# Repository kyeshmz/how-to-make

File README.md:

https://fab.cba.mit.edu/classes/MAS.863/

```
for img in *.jpg; do [ -f "$img" ] && magick "$img" -resize 1200x "$img"; done
```

https://ui.aceternity.com/components

https://fab.cba.mit.edu/classes/MAS.863/

for hardware
https://fabacademy.org/2022/labs/kamplintfort/students/leen-nijim/assignments/seven.html

#!/bin/bash

# Find all .jpg files in the current directory and subdirectories
find . -type f -name "*.jpg" | while read img; do
    # Resize each image to a width of 1200px, maintaining aspect ratio
    magick "$img" -resize 1200x "$img"
done

ffmpeg -i input_video -vcodec libx264 -b:v 1000k -vf scale=-2:1080 -an output_video.mp4

change mods cut depth to 0.15

for video in ./*.mp4; do ffmpeg -i "$video" -vcodec libx264 -b:v 1000k -vf scale=-2:1080 -an "${video%.*}_reformatted.mp4"; done

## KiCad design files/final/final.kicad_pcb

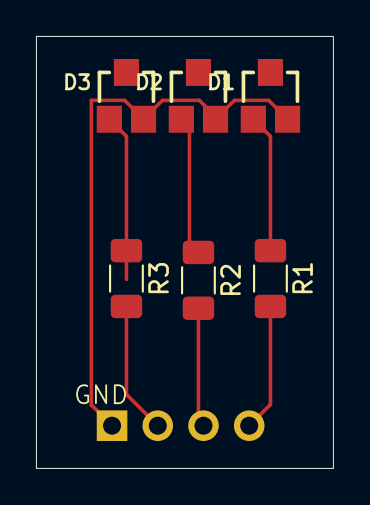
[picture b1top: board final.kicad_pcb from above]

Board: 2 copper layers, 16.5 x 24.0 mm, 7 parts (1 on the bottom side), 7 nets.

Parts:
D1, D2, D3: LED; SML-LX15
J1: Conn_01x04_Pin; PinHeader_1x04_P2.54mm_Horizontal
R1, R2, R3: R; R_1206_3216Metric_Pad1.30x1.75mm_HandSolder

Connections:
unnamed: D1.2 (A), R1.1
unnamed: D1.1 (K), D2.1 (K), D3.1 (K), J1.1
unnamed: D2.2 (A), R2.1
unnamed: D3.2 (A), R3.1
unnamed: J1.2, R3.2
unnamed: J1.3, R2.2
unnamed: J1.4, R1.2

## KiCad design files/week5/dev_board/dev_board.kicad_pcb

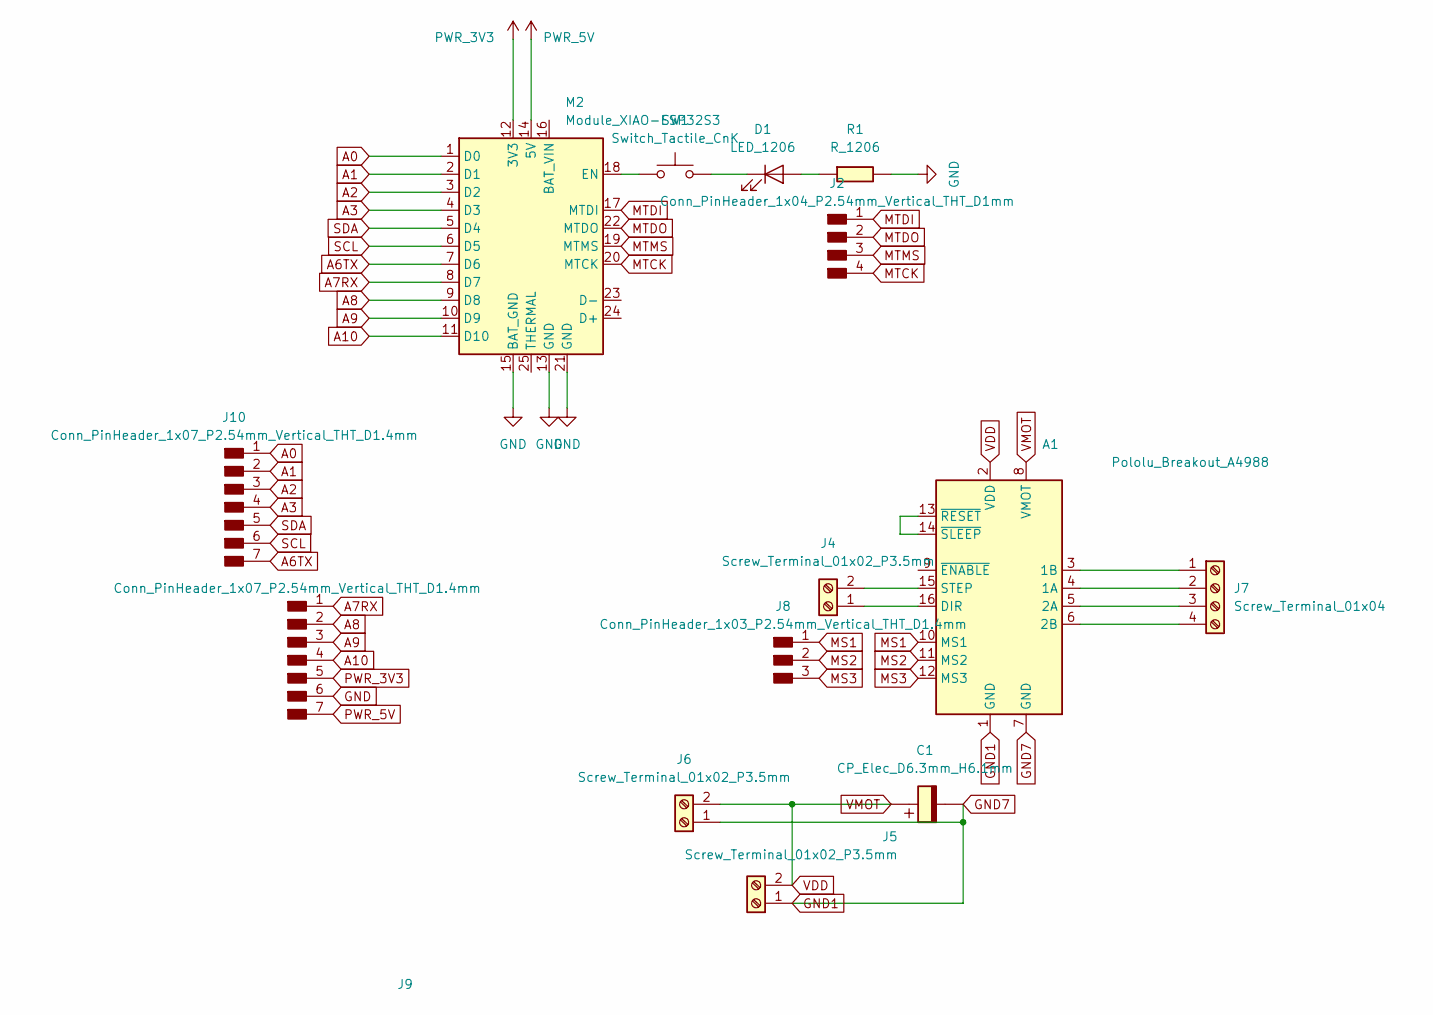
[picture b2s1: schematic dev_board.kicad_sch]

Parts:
A1: Pololu_Breakout_A4988; Pololu_Breakout-16_15.2x20.3mm
C1: CP_Elec_D6.3mm_H6.1mm
D1: LED_1206
J2: Conn_PinHeader_1x04_P2.54mm_Vertical_THT_D1mm; PinHeader_1x04_P2.54mm_Vertical_THT_D1mm
J4, J5, J6: Screw_Terminal_01x02_P3.5mm; TerminalBlock_OnShore_1x02_P3.50mm_Horizontal
J7: Screw_Terminal_01x04
J8: Conn_PinHeader_1x03_P2.54mm_Vertical_THT_D1.4mm; PinHeader_1x03_P2.54mm_Vertical_THT_D1.4mm
J9, J10: Conn_PinHeader_1x07_P2.54mm_Vertical_THT_D1.4mm; PinHeader_1x07_P2.54mm_Vertical_THT_D1.4mm
M2: Module_XIAO-ESP32S3; SeeedStudio_XIAO_ESP32S3
R1: R_1206
SW1: Switch_Tactile_CnK; Button_CnK_PTS636.0_6x3.5mm

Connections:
A0: J10.1, M2.1 (D0)
A1: J10.2, M2.2 (D1)
A2: J10.3, M2.3 (D2)
A3: J10.4, M2.4 (D3)
A6TX: J10.7, M2.7 (D6)
A7RX: J9.1, M2.8 (D7)
A8: J9.2, M2.9 (D8)
A9: J9.3, M2.10 (D9)
A10: J9.4, M2.11 (D10)
GND: J9.6, M2.13 (GND), M2.15 (BAT_GND), M2.21 (GND), R1.1
GND1: A1.1 (GND), A1.7 (GND), C1.2, J5.1, J6.1
MS1: A1.10 (MS1), J8.1
MS2: A1.11 (MS2), J8.2
MS3: A1.12 (MS3), J8.3
MTCK: J2.4, M2.20 (MTCK)
MTDI: J2.1, M2.17 (MTDI)
MTDO: J2.2, M2.22 (MTDO)
MTMS: J2.3, M2.19 (MTMS)
unnamed: A1.4 (1A), J7.2
unnamed: A1.3 (1B), J7.1
unnamed: A1.5 (2A), J7.3
unnamed: A1.6 (2B), J7.4
unnamed: A1.16 (DIR), J4.1
unnamed: A1.15 (STEP), J4.2
unnamed: A1.13 (~RESET), A1.14 (~SLEEP)
unnamed: D1.2 (A), R1.2
unnamed: D1.1 (K), SW1.2
unnamed: M2.18 (EN), SW1.1
PWR_3V3: J9.5, M2.12 (3V3)
PWR_5V: J9.7, M2.14 (5V)
SCL: J10.6, M2.6 (D5)
SDA: J10.5, M2.5 (D4)
VDD: A1.2 (VDD), A1.8 (VMOT), C1.1, J5.2, J6.2

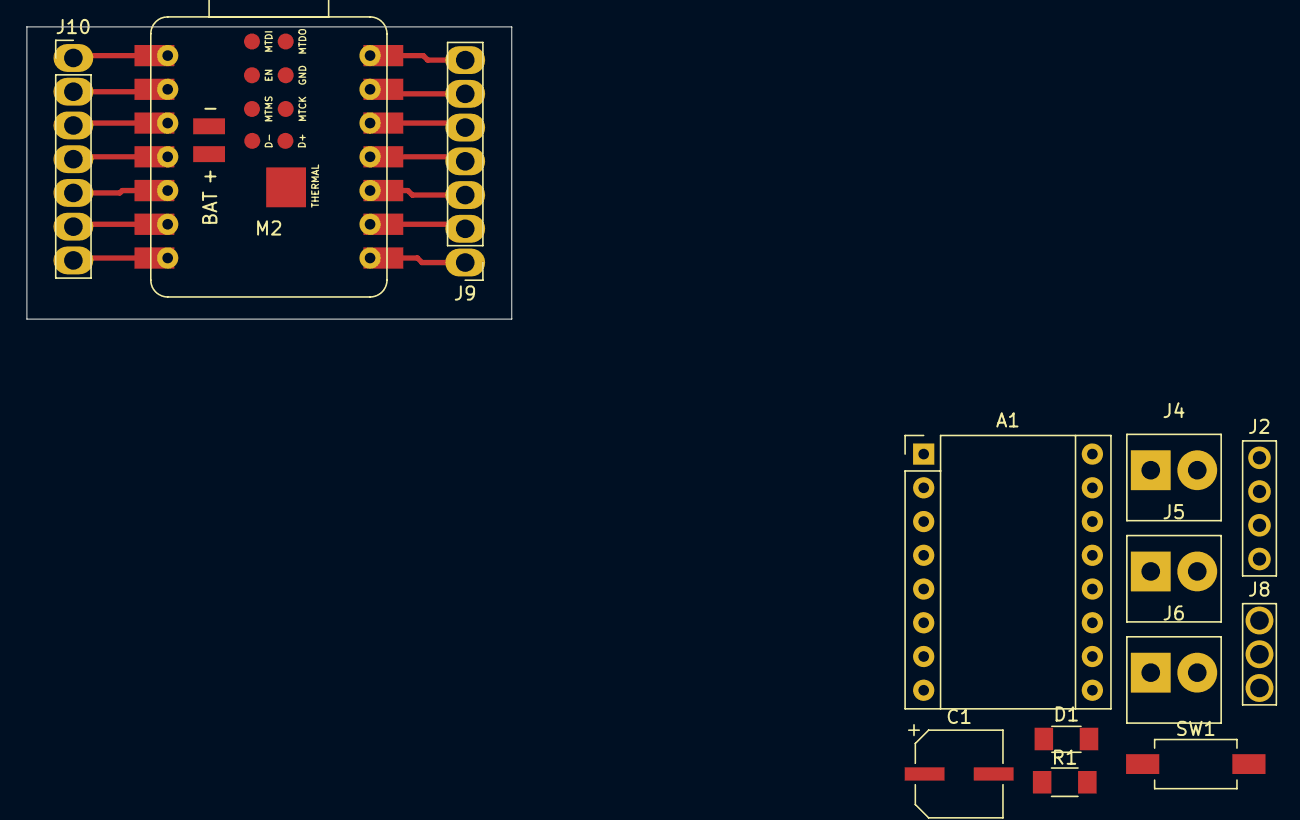
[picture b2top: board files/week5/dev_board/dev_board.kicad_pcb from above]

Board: 2 copper layers, 36.5 x 22.0 mm, 13 parts (0 on the bottom side), 29 nets.

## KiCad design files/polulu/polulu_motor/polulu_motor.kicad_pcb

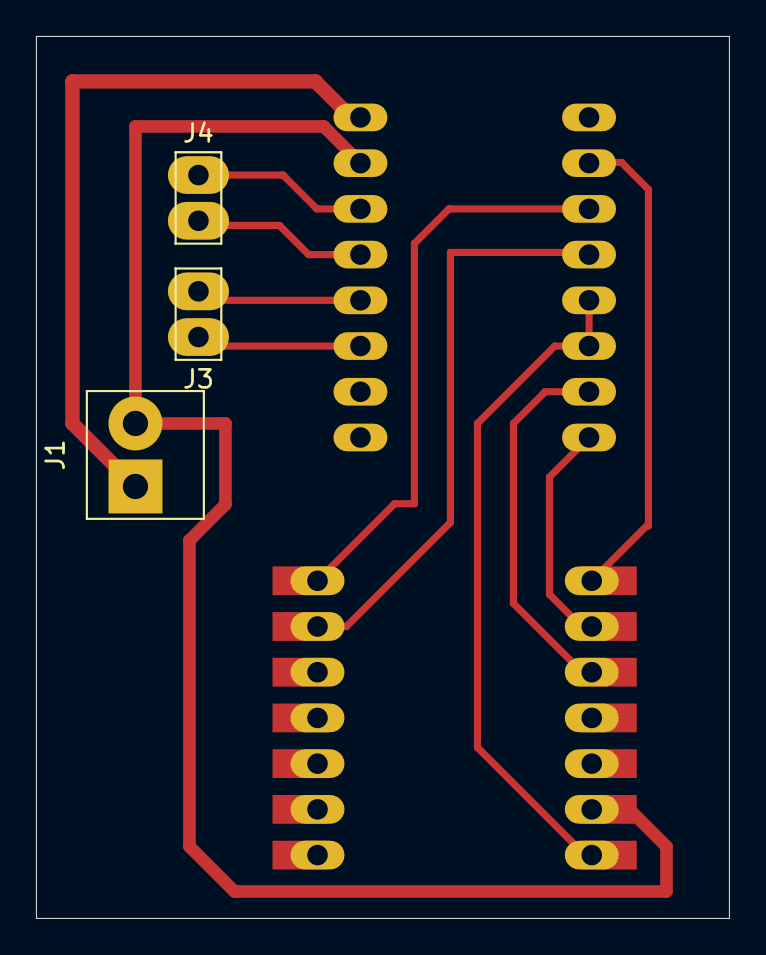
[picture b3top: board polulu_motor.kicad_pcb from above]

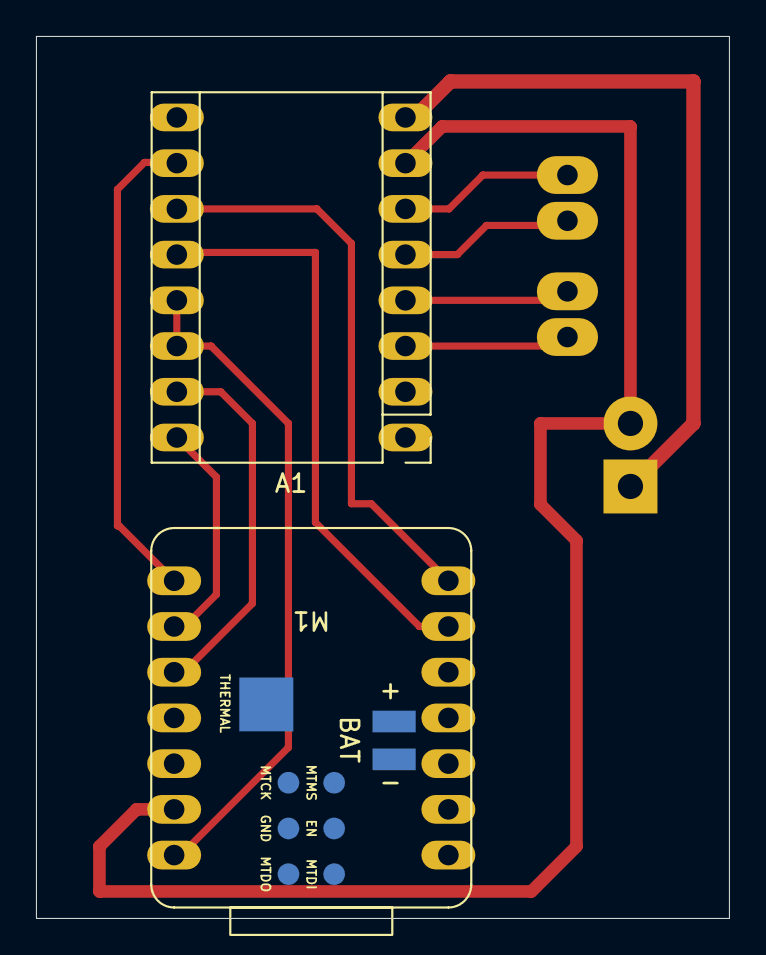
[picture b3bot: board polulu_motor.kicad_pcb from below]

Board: 2 copper layers, 38.5 x 49.0 mm, 5 parts (2 on the bottom side), 13 nets.

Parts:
A1: Pololu_Breakout_DRV8825; Pololu_Breakout-16_15.2x20.3mm
J1: Screw_Terminal_01x02_P3.5mm; TerminalBlock_OnShore_1x02_P3.50mm_Horizontal
J3, J4: Conn_PinHeader_1x02_P2.54mm_Vertical_THT_D1.4mm; PinHeader_1x02_P2.54mm_Vertical_THT_D1.4mm
M1: Module_XIAO-ESP32C3; SeeedStudio_XIAO_ESP32C3_flipped

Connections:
GND1: A1.7 (GND), J1.2, M1.13 (GND)
unnamed: A1.4 (A1), J3.2
unnamed: A1.3 (A2), J3.1
unnamed: A1.5 (B1), J4.2
unnamed: A1.6 (B2), J4.1
unnamed: A1.16 (DIR), M1.9 (D8)
unnamed: A1.10 (M0), M1.8 (D7)
unnamed: A1.11 (M1), M1.7 (D6)
unnamed: A1.12 (M2), M1.6 (D5)
unnamed: A1.15 (STEP), M1.10 (D9)
unnamed: A1.9 (~EN), M1.11 (D10)
unnamed: A1.13 (~RST), A1.14 (~SLP), M1.14 (5V)
VMOT1: A1.8 (VMOT), J1.1

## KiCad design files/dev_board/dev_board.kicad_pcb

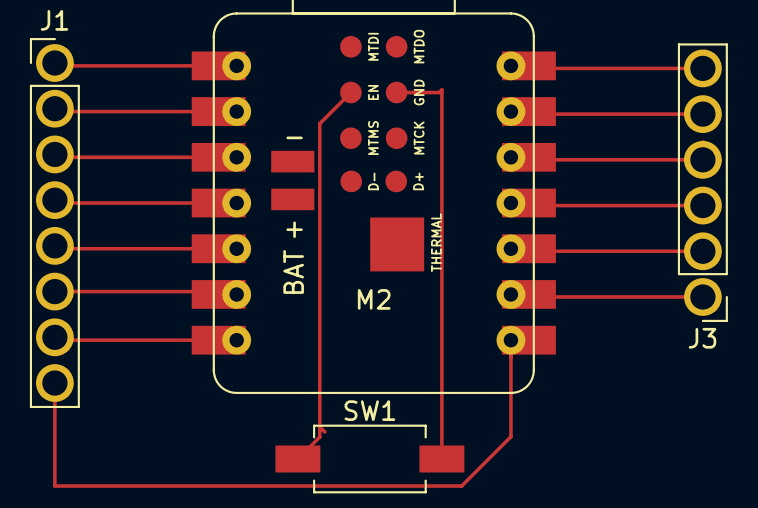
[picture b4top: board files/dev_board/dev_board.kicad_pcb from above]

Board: 2 copper layers, 4 parts (0 on the bottom side), 15 nets.

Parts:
J1: Conn_PinHeader_1x08_P2.54mm_Vertical_THT_D1.4mm; PinHeader_1x08_P2.54mm_Vertical_THT_D1.4mm
J3: Conn_PinHeader_1x06_P2.54mm_Vertical_THT_D1.4mm; PinHeader_1x06_P2.54mm_Vertical_THT_D1.4mm
M2: Module_XIAO-ESP32S3; SeeedStudio_XIAO_ESP32S3
SW1: Switch_Tactile_CnK; Button_CnK_PTS636.0_6x3.5mm

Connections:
A0: J1.1, M2.1 (D0)
A1: J1.2, M2.2 (D1)
A2: J1.3, M2.3 (D2)
A3: J1.4, M2.4 (D3)
A6TX: J1.7, M2.7 (D6)
A7RX: J1.8, M2.8 (D7)
A8: J3.1, M2.9 (D8)
A9: J3.2, M2.10 (D9)
A10: J3.3, M2.11 (D10)
GND: J3.5, M2.13 (GND), M2.15 (BAT_GND), M2.21 (GND), SW1.2
unnamed: M2.18 (EN), SW1.1
PWR_3V3: J3.4, M2.12 (3V3)
PWR_5V: J3.6, M2.14 (5V)
SCL: J1.6, M2.6 (D5)
SDA: J1.5, M2.5 (D4)

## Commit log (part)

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2024-09-10 add all
2024-09-10 Add renovate.json
2024-09-11 fix headers
2024-09-11 remove the search
2024-09-11 ffix the layout
2024-09-11 fix padding
2024-09-12 add new deploy script
2024-09-12 fix git ignore
2024-09-12 copy workflow file to public
2024-09-12 try using bun
2024-09-12 try merging
2024-09-12 fix final site
2024-09-12 dont force all
2024-09-12 just reset each time
2024-09-12 fuck it force
2024-09-12 try using base
2024-09-12 fix to use ignore
2024-09-12 fix base
2024-09-12 fix base tag
2024-09-12 fix links
2024-09-12 try this
2024-09-12 fix relative links
2024-09-12 try removing base
2024-09-12 try new base
2024-09-12 fix urls
2024-09-12 try done
2024-09-12 fix base url
2024-09-12 try adding base
2024-09-12 remove view transitions
2024-09-12 remove base
2024-09-12 fix base to none
2024-09-12 remove menu
2024-09-12 fix relative
2024-09-12 fix gitlab
2024-09-12 fix to use npm ci
2024-09-12 add install script
2024-09-12 fix bashrc
2024-09-12 remove ci
2024-09-12 add public
2024-09-14 Update astro monorepo
2024-09-14 remove everything other than public
2024-09-15 add new week 2 stuff
2024-09-15 push to work
2024-09-15 fix undefine
2024-09-15 fix tags
2024-09-16 fix image res
2024-09-16 add files
2024-09-16 fix content
2024-09-16 remove images
2024-09-16 optimize images
2024-09-17 fix week2
2024-09-17 dish out one size
2024-09-17 fix import
2024-09-17 resize images
2024-09-17 remove site packages
2024-09-18 add agreement
2024-09-18 push assets
2024-09-18 optimize
2024-09-18 fix pictures
2024-09-18 fix final aliases
2024-09-18 remove tags
2024-09-24 add week3
2024-09-24 remove unused
2024-09-24 add cat
2024-09-25 fix typign
2024-09-25 fixcat sizing
2024-09-25 add new assignment for week4
2024-09-25 add content
2024-09-25 fix about to use markdown
2024-09-29 add week4
2024-09-29 add more links
2024-09-29 fix packages
2024-09-29 update adn fix bun version in cloud
2024-09-29 fix to use dist
2024-09-30 add 3d file
2024-09-30 fix week4 for models
2024-09-30 remove console
2024-09-30 fix week4 ones
2024-10-01 Bump @react-three/fiber from 8.17.8 to 8.17.9
    Bumps [@react-three/fiber](https://github.com/pmndrs/react-three-fiber) from 8.17.8 to 8.17.9.
    - [Release notes](https://github.com/pmndrs/react-three-fiber/releases)
    - [Commits](https://github.com/pmndrs/react-three-fiber/compare/v8.17.8...v8.17.9)
    ---
    updated-dependencies:
    - dependency-name: "@react-three/fiber"
2024-10-01 Bump astro from 4.15.9 to 4.15.10
    Bumps [astro](https://github.com/withastro/astro/tree/HEAD/packages/astro) from 4.15.9 to 4.15.10.
    - [Release notes](https://github.com/withastro/astro/releases)
    - [Changelog](https://github.com/withastro/astro/blob/main/packages/astro/CHANGELOG.md)
    - [Commits](https://github.com/withastro/astro/commits/astro@4.15.10/packages/astro)
    ---
    updated-dependencies:
2024-10-02 Bump @types/react from 18.3.9 to 18.3.10
    Bumps [@types/react](https://github.com/DefinitelyTyped/DefinitelyTyped/tree/HEAD/types/react) from 18.3.9 to 18.3.10.
    - [Release notes](https://github.com/DefinitelyTyped/DefinitelyTyped/releases)
    - [Commits](https://github.com/DefinitelyTyped/DefinitelyTyped/commits/HEAD/types/react)
    ---
    updated-dependencies:
    - dependency-name: "@types/react"
2024-10-02 update packages
2024-10-02 add about
2024-10-02 fix tsignore
2024-10-02 fix a bit of final
2024-10-08 fix directory layout
2024-10-09 add boards and stuff
2024-10-16 fix final
2024-10-16 fix for shiki
2024-10-16 fix iimg
2024-10-16 fix font for about
2024-10-16 fix title
2024-10-23 fix images
2024-10-23 fix image
2024-10-23 fix about
2024-10-23 use image
2024-10-23 add houdini ring
2024-10-23 add images
2024-10-23 add some notes
2024-10-23 add a void documentation
2024-10-23 hopefully fix
2024-10-30 week8
2024-10-30 fix gitignore
2024-10-30 fix cover
2024-11-01 Bump @rive-app/canvas-lite from 2.22.0 to 2.23.2
    Bumps [@rive-app/canvas-lite](https://github.com/rive-app/rive-wasm) from 2.22.0 to 2.23.2.
    - [Changelog](https://github.com/rive-app/rive-wasm/blob/master/CHANGELOG.md)
    - [Commits](https://github.com/rive-app/rive-wasm/compare/2.22.0...2.23.2)
    ---
    updated-dependencies:
    - dependency-name: "@rive-app/canvas-lite"
2024-11-01 Bump three from 0.169.0 to 0.170.0
    Bumps [three](https://github.com/mrdoob/three.js) from 0.169.0 to 0.170.0.
    - [Release notes](https://github.com/mrdoob/three.js/releases)
    - [Commits](https://github.com/mrdoob/three.js/commits)
    ---
    updated-dependencies:
    - dependency-name: three
2024-11-06 fix file caching
2024-11-06 add week9
2024-11-06 only one image
2024-11-06 try pushing without files
2024-11-06 Bump @types/react from 18.3.11 to 18.3.12
    Bumps [@types/react](https://github.com/DefinitelyTyped/DefinitelyTyped/tree/HEAD/types/react) from 18.3.11 to 18.3.12.
    - [Release notes](https://github.com/DefinitelyTyped/DefinitelyTyped/releases)
    - [Commits](https://github.com/DefinitelyTyped/DefinitelyTyped/commits/HEAD/types/react)
    ---
    updated-dependencies:
    - dependency-name: "@types/react"
2024-11-06 Bump @astrojs/mdx from 3.1.8 to 3.1.9
    Bumps [@astrojs/mdx](https://github.com/withastro/astro/tree/HEAD/packages/integrations/mdx) from 3.1.8 to 3.1.9.
    - [Release notes](https://github.com/withastro/astro/releases)
    - [Changelog](https://github.com/withastro/astro/blob/main/packages/integrations/mdx/CHANGELOG.md)
    - [Commits](https://github.com/withastro/astro/commits/@astrojs/mdx@3.1.9/packages/integrations/mdx)
    ---
    updated-dependencies:
2024-11-06 Bump @types/react-dom from 18.3.0 to 18.3.1
    Bumps [@types/react-dom](https://github.com/DefinitelyTyped/DefinitelyTyped/tree/HEAD/types/react-dom) from 18.3.0 to 18.3.1.
    - [Release notes](https://github.com/DefinitelyTyped/DefinitelyTyped/releases)
    - [Commits](https://github.com/DefinitelyTyped/DefinitelyTyped/commits/HEAD/types/react-dom)
    ---
    updated-dependencies:
    - dependency-name: "@types/react-dom"
2024-11-06 Bump @rive-app/canvas-lite from 2.23.0 to 2.23.4
    Bumps [@rive-app/canvas-lite](https://github.com/rive-app/rive-wasm) from 2.23.0 to 2.23.4.
    - [Changelog](https://github.com/rive-app/rive-wasm/blob/master/CHANGELOG.md)
    - [Commits](https://github.com/rive-app/rive-wasm/compare/2.23.0...2.23.4)
    ---
    updated-dependencies:
    - dependency-name: "@rive-app/canvas-lite"
2024-11-06 Update react monorepo
2024-11-06 fix week 9
2024-11-06 resize all images
2024-11-06 fix videos
2024-11-06 fix dependencies
2024-11-06 fix to add to dist instead of public
2024-11-06 fix cover images
2024-11-06 add back all files
2024-11-13 fix package locks
2024-11-13 fix bun
2024-11-13 add solver image
2024-11-13 fix pub date
2024-11-13 fix the final date to be the last
2024-11-13 add files for week10
2024-11-13 add files for recreation
2024-11-13 fix class or classname
2024-11-13 add zip files for up to week 5
2024-11-15 fix typing
2024-11-15 pub date
2024-11-15 make new one for this week
2024-11-20 add some week11
2024-11-20 fix building process
2024-11-20 use action
2024-11-20 Update withastro/action action to v3
2024-11-20 fix to optimize images
2024-11-20 fix to not have big f3d file
2024-11-20 add week11 server things
2024-11-27 add this weeks stuff
2024-11-27 add deps
2024-11-27 fix the devboard
2024-12-01 Bump three from 0.170.0 to 0.171.0
    Bumps [three](https://github.com/mrdoob/three.js) from 0.170.0 to 0.171.0.
    - [Release notes](https://github.com/mrdoob/three.js/releases)
    - [Commits](https://github.com/mrdoob/three.js/commits)
    ---
    updated-dependencies:
    - dependency-name: three
2024-12-01 Bump @types/three from 0.169.0 to 0.170.0
    Bumps [@types/three](https://github.com/DefinitelyTyped/DefinitelyTyped/tree/HEAD/types/three) from 0.169.0 to 0.170.0.
    - [Release notes](https://github.com/DefinitelyTyped/DefinitelyTyped/releases)
    - [Commits](https://github.com/DefinitelyTyped/DefinitelyTyped/commits/HEAD/types/three)
    ---
    updated-dependencies:
    - dependency-name: "@types/three"
2024-12-04 add barely
2024-12-04 add electron
2024-12-04 fix files
2024-12-04 add more to site
2024-12-11 add videos
2024-12-11 add some more
2024-12-12 fix sktch
2024-12-15 add initial
2024-12-17 add some files from project
2024-12-18 Update dependency astro to v5
2024-12-18 fix movie
2024-12-18 Committing the final chunk of files
2024-12-19 fix add
2024-12-19 Bump three and @types/three
    Bumps [three](https://github.com/mrdoob/three.js) and [@types/three](https://github.com/DefinitelyTyped/DefinitelyTyped/tree/HEAD/types/three). These dependencies needed to be updated together.
    Updates `three` from 0.170.0 to 0.171.0
    - [Release notes](https://github.com/mrdoob/three.js/releases)
    - [Commits](https://github.com/mrdoob/three.js/commits)
    Updates `@types/three` from 0.169.0 to 0.171.0
    - [Release notes](https://github.com/DefinitelyTyped/DefinitelyTyped/releases)
2025-01-01 Bump tailwindcss from 3.4.14 to 3.4.17
    Bumps [tailwindcss](https://github.com/tailwindlabs/tailwindcss) from 3.4.14 to 3.4.17.
    - [Release notes](https://github.com/tailwindlabs/tailwindcss/releases)
    - [Changelog](https://github.com/tailwindlabs/tailwindcss/blob/v3.4.17/CHANGELOG.md)
    - [Commits](https://github.com/tailwindlabs/tailwindcss/compare/v3.4.14...v3.4.17)
    ---
    updated-dependencies:
2025-01-01 Bump @astrojs/react from 4.1.1 to 4.1.2
    Bumps [@astrojs/react](https://github.com/withastro/astro/tree/HEAD/packages/integrations/react) from 4.1.1 to 4.1.2.
    - [Release notes](https://github.com/withastro/astro/releases)
    - [Changelog](https://github.com/withastro/astro/blob/main/packages/integrations/react/CHANGELOG.md)
    - [Commits](https://github.com/withastro/astro/commits/@astrojs/react@4.1.2/packages/integrations/react)
    ---
    updated-dependencies:
2025-01-01 Bump astro from 5.0.9 to 5.1.1
    Bumps [astro](https://github.com/withastro/astro/tree/HEAD/packages/astro) from 5.0.9 to 5.1.1.
    - [Release notes](https://github.com/withastro/astro/releases)
    - [Changelog](https://github.com/withastro/astro/blob/main/packages/astro/CHANGELOG.md)
    - [Commits](https://github.com/withastro/astro/commits/astro@5.1.1/packages/astro)
    ---
    updated-dependencies:
2025-01-01 Bump preline from 2.5.1 to 2.6.0
    Bumps [preline](https://github.com/htmlstreamofficial/preline) from 2.5.1 to 2.6.0.
    - [Release notes](https://github.com/htmlstreamofficial/preline/releases)
    - [Commits](https://github.com/htmlstreamofficial/preline/compare/v2.5.1...v2.6.0)
    ---
    updated-dependencies:
    - dependency-name: preline
2025-02-01 Bump preline from 2.5.1 to 2.7.0
    Bumps [preline](https://github.com/htmlstreamofficial/preline) from 2.5.1 to 2.7.0.
    - [Release notes](https://github.com/htmlstreamofficial/preline/releases)
    - [Commits](https://github.com/htmlstreamofficial/preline/compare/v2.5.1...v2.7.0)
    ---
    updated-dependencies:
    - dependency-name: preline
2025-02-01 Bump @astrojs/react from 4.1.1 to 4.2.0
    Bumps [@astrojs/react](https://github.com/withastro/astro/tree/HEAD/packages/integrations/react) from 4.1.1 to 4.2.0.
    - [Release notes](https://github.com/withastro/astro/releases)
    - [Changelog](https://github.com/withastro/astro/blob/main/packages/integrations/react/CHANGELOG.md)
    - [Commits](https://github.com/withastro/astro/commits/@astrojs/react@4.2.0/packages/integrations/react)
    ---
    updated-dependencies:
2025-02-01 Bump astro from 5.0.9 to 5.2.3
    Bumps [astro](https://github.com/withastro/astro/tree/HEAD/packages/astro) from 5.0.9 to 5.2.3.
    - [Release notes](https://github.com/withastro/astro/releases)
    - [Changelog](https://github.com/withastro/astro/blob/main/packages/astro/CHANGELOG.md)
    - [Commits](https://github.com/withastro/astro/commits/astro@5.2.3/packages/astro)
    ---
    updated-dependencies:
